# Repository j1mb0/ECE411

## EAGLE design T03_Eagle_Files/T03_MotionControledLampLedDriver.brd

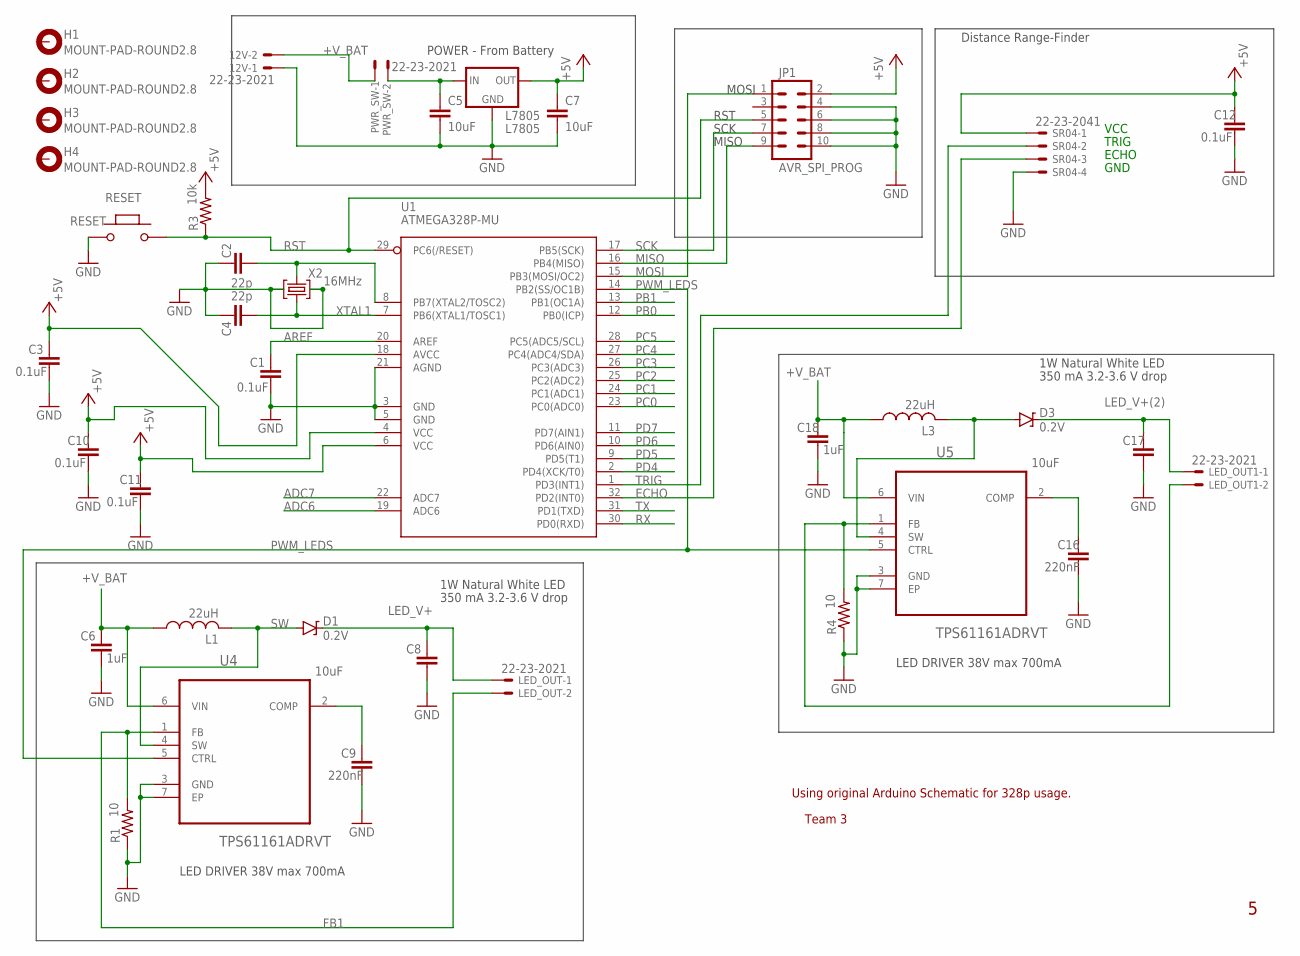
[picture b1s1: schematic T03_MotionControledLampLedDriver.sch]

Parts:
12V: 22-23-2021
C1, C3, C10, C11, C12: 0.1uF; C0603-ROUND
C2, C4: 22p; C0603-ROUND
C5, C7: 10uF; C1206
C6, C18: 1uF; C0603-ROUND
C8, C17: 10uF; C0603-ROUND
C9, C16: 220nF; C0603-ROUND
D1, D3: 0.2V; SOD-323
H1, H2, H3, H4: MOUNT-PAD-ROUND2.8; 2,8-PAD
JP1: AVR_SPI_PROG; 2X5-SHROUDED_LOCK
L1, L3: 22uH; L4532P
L7805: L7805; 78XXL
LED_OUT, LED_OUT1: 22-23-2021
PWR_SW: 22-23-2021
R1, R4: 10; M1206
R3: 10k; M1206
RESET: RESET; SMD_157SW
SR04: 22-23-2041
U1: ATMEGA328P-MU; TQFP32-08
U4, U5: TPS61161ADRVT; SON65P200X200X80-7N
X2: 16MHz; CRYSTAL-3.2-2.5

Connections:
+5V: C3.2, C7.1, C10.2, C11.2, C12.2, JP1.2, L7805.OUT, R3.2, SR04.1, U1.4 (VCC), U1.6 (VCC), U1.18 (AVCC)
+V_BAT: 12V.2, C6.2, C18.2, L1.1, L3.1, PWR_SW.1, U4.6 (VIN), U5.6 (VIN)
ADC6: U1.19 (ADC6)
ADC7: U1.22 (ADC7)
AREF: C1.2, U1.20 (AREF)
COMP: C9.2, U4.2 (COMP)
COMP1: C16.2, U5.2 (COMP)
ECHO: SR04.3, U1.32 (PD2(INT0))
FB1: LED_OUT.2, R1.2, U4.1 (FB)
FB2: LED_OUT1.2, R4.2, U5.1 (FB)
GND: 12V.1, C1.1, C2.2, C3.1, C4.2, C5.2, C6.1, C7.2, C8.1, C9.1, C10.1, C11.1, C12.1, C16.1, C17.1, C18.1, JP1.4, JP1.6, JP1.8, JP1.10, L7805.GND, R1.1, R4.1, RESET.1, SR04.4, U1.3 (GND), U1.5 (GND), U1.21 (AGND), U4.3 (GND), U4.7 (EP), U5.3 (GND), U5.7 (EP), X2.2 (GND), X2.4 (GND)
LED_V+: C8.2, D1.C, LED_OUT.1
LED_V+(2): C17.2, D3.C, LED_OUT1.1
MISO: JP1.9, U1.16 (PB4(MISO))
MOSI: JP1.1, U1.15 (PB3(MOSI/OC2))
unnamed: C5.1, L7805.IN, PWR_SW.2
PB0: U1.12 (PB0(ICP))
PB1: U1.13 (PB1(OC1A))
PC0: U1.23 (PC0(ADC0))
PC1: U1.24 (PC1(ADC1))
PC2: U1.25 (PC2(ADC2))
PC3: U1.26 (PC3(ADC3))
PC4: U1.27 (PC4(ADC4/SDA))
PC5: U1.28 (PC5(ADC5/SCL))
PD4: U1.2 (PD4(XCK/T0))
PD5: U1.9 (PD5(T1))
PD6: U1.10 (PD6(AIN0))
PD7: U1.11 (PD7(AIN1))
PWM_LEDS: U1.14 (PB2(SS/OC1B)), U4.5 (CTRL), U5.5 (CTRL)
RST: JP1.5, R3.1, RESET.2, U1.29 (PC6(/RESET))
RX: U1.30 (PD0(RXD))
SCK: JP1.7, U1.17 (PB5(SCK))
SW: D1.A, L1.2, U4.4 (SW)
SW1: D3.A, L3.2, U5.4 (SW)
TRIG: SR04.2, U1.1 (PD3(INT1))
TX: U1.31 (PD1(TXD))
XTAL1: C4.1, U1.7 (PB6(XTAL1/TOSC1)), X2.1 (C1)
XTAL2: C2.1, U1.8 (PB7(XTAL2/TOSC2)), X2.3 (C2)

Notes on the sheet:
POWER - From Battery
Distance Range-Finder
RST
MISO
SCK
MOSI
LED DRIVER 38V max 700mA
1W Natural White LED
350 mA 3.2-3.6 V drop
Using original Arduino Schematic for 328p usage.
Team 3
VCC
TRIG
ECHO
GND

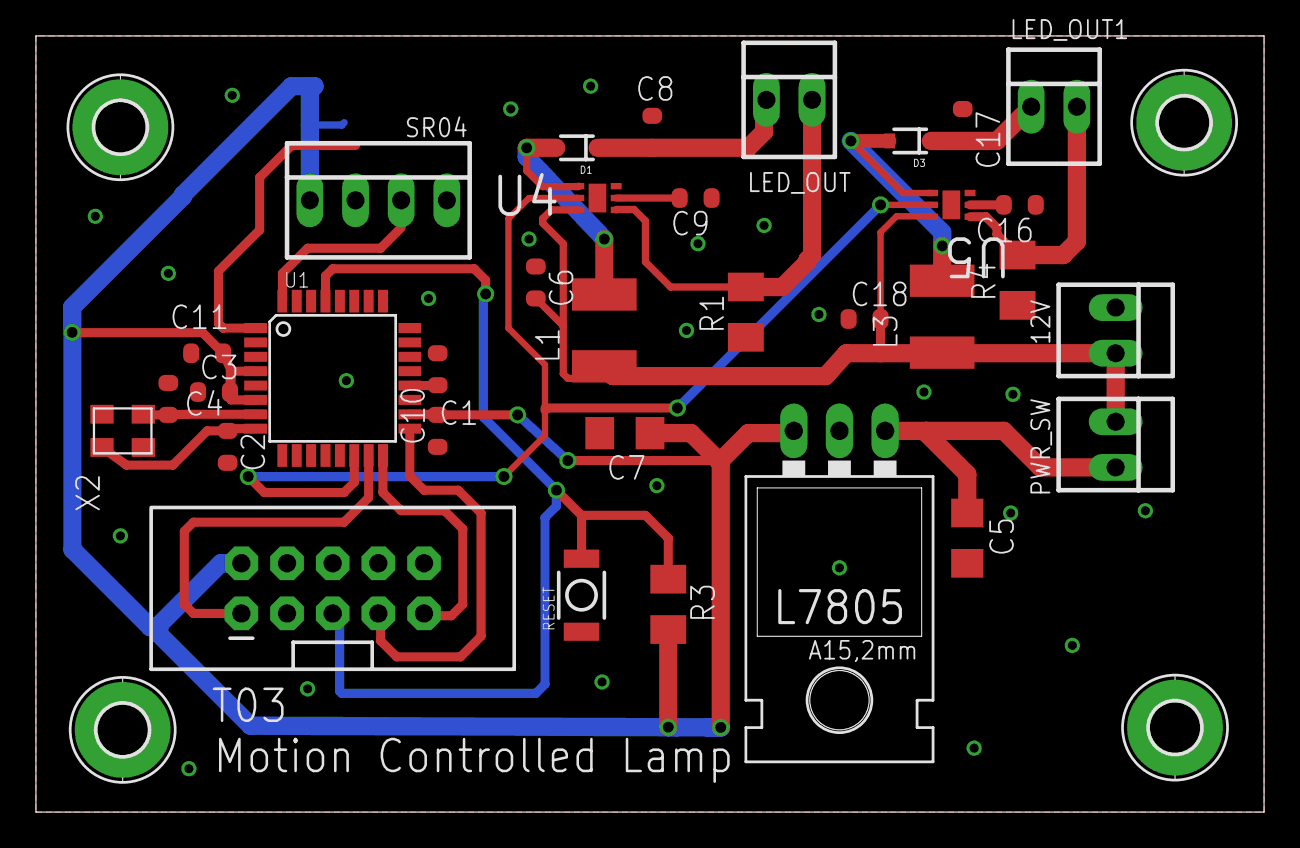
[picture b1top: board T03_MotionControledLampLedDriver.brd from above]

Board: 2 copper layers, 68.3 x 43.2 mm, 38 parts (1 on the bottom side), 22 nets.

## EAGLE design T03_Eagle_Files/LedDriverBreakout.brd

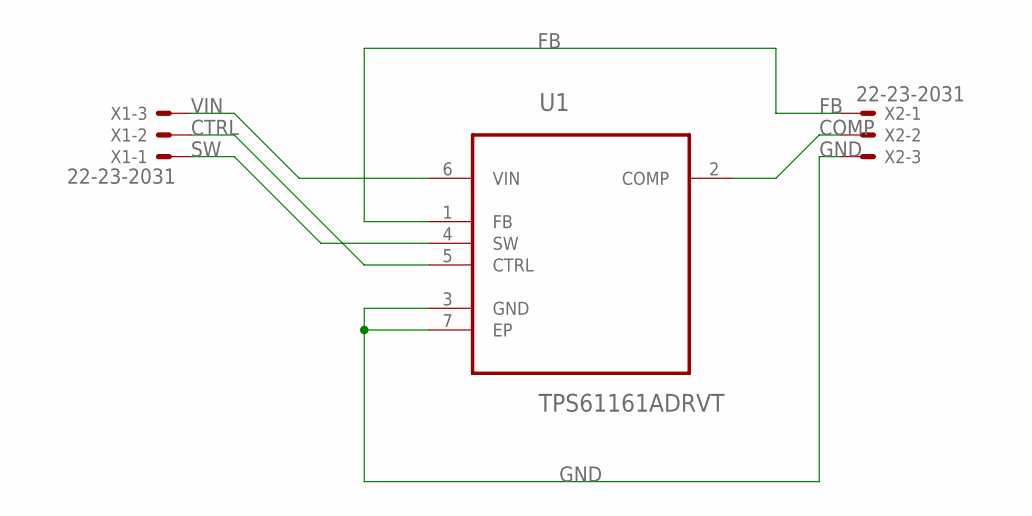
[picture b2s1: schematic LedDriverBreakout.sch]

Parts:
U1: TPS61161ADRVT; SON65P200X200X80-7N
X1, X2: 22-23-2031

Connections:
COMP: U1.2 (COMP), X2.2
CTRL: U1.5 (CTRL), X1.2
FB: U1.1 (FB), X2.1
GND: U1.3 (GND), U1.7 (EP), X2.3
SW: U1.4 (SW), X1.1
VIN: U1.6 (VIN), X1.3

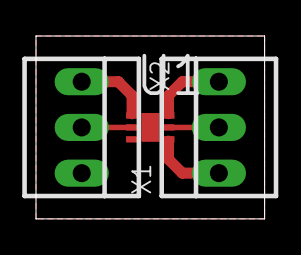
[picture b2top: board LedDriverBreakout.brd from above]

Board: 2 copper layers, 12.7 x 10.2 mm, 3 parts (0 on the bottom side), 6 nets.

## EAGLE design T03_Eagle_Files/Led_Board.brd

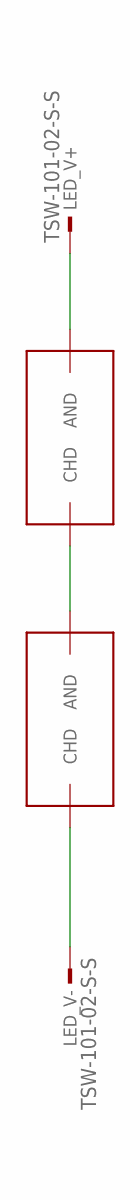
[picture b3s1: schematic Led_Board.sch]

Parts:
LED_V+: TSW-101-02-S-S
LED_V-: TSW-101-02-S-S
U$1, U$2: TL1F2-NW1

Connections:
unnamed: LED_V-.1, U$2.CATHODE (CHD)
unnamed: U$1.CATHODE (CHD), U$2.ANODE (AND)
unnamed: LED_V+.1, U$1.ANODE (AND)

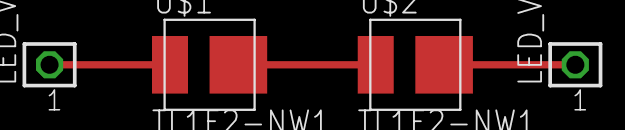
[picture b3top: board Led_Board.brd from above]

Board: 2 copper layers, 4 parts (0 on the bottom side), 3 nets.

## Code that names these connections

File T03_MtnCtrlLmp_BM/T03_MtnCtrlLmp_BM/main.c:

/*
 * T03_MtnCtrlLmp_BM.c
 *
 * Created: 11/27/2015 10:10:34 AM
 * Author : J1mb0
 * Motion Controlled Lamp using SR04 Ultrasonic Sensor
 * And custom Power NFET LED Driver.
 * 16 Mhz 62.5 ns Clock
 * Use prescale of 256 to get 16 us resolution on clock
 * with a range of 4 mS
 * Want response under 10 ms
 * Maybe not possible, SR04 has recommended read cycle of at least 60 ms
 */ 

#include <avr/io.h>
#define F_CPU 16000000UL //16 MHz
#include <util/delay.h>

#define MAX_PULSE_WIDTH 139 // 16 us * 139 ~= 2220 us
#define TIME_OUT 60		// 60 ms measurement cycle
#define MILLI_SECOND 64 // 16 us * 64 = 1024 uS or 1 mS 
#define US_ERROR 0xFFFF
// Ultrasonic Sensor (US) pin configuration
#define US_PORT PORTD
#define US_PIN PIND
#define US_DDR DDRD
#define US_ECHO_POS PORTD2
#define US_TRIG_POS PORTD3
// PWM conversion factors
#define MINIMUM_DISTANCE 27 // (3 in * 148)/ 16 uS = 27.75 rounded down 
#define MICROSEC_TO_PWM 2.28f // 2^8 / (139 - 27) ~= 2.28, our conversion factor

uint16_t getPulseWidth()
{
	uint16_t i, savedTimer, result, millisCount;
	
	i = 0;
	result = US_ERROR;		// Timed out code
	millisCount = 0;
	
	// set up timer
	TCCR0A = 0x00;
	TCCR0B = (1<<CS02);  // Prescaler = Fcpu/256
	TCNT0 = 0;			// Init Counter to 0
	
	// wait for the rising edge of ECHO or until time out
	while(millisCount < TIME_OUT && !(US_PIN & (1<<US_ECHO_POS)))
	{
		if(TCNT0 >= MILLI_SECOND)
		{
			TCNT0 = 0;
			millisCount++;
		}
	}
	// stop timer - I DO NOT THINK WE NEED TO DO THIS
	//CCR0B = 0x00 
	// Reset the timer
	//TCNT0 = 0;
	// Start timer again 
	//TCCR0B |= (1<<CS02);
	savedTimer = TCNT0;
	
	// Now wait for the falling edge or for the measurement to time out
	while((i - savedTimer) < MAX_PULSE_WIDTH && US_PIN & (1<<US_ECHO_POS))
	{
		i = TCNT0;
	}
	
	// if it did not time out, save the timer value
	if(i < MAX_PULSE_WIDTH)
	{
		result = i;
	}
	
	while(millisCount < MILLI_SECOND)
	{
		if(TCNT0 >= MILLI_SECOND)
		{
			TCNT0 = 0;
			millisCount++;
		}
	}
	
	// TURN OFF TIMER0
	TCCR0B = 0x00;
	
	return result;	
}

int main(void)
{
    uint16_t  i, result, averageResult;
	uint8_t pwmOut;
	pwmOut = 0;
	
	// Set Output/Input modes for pins
	// PWM_LEDS (PB2) as output (set 1)
	DDRB |= (1<<DDB2);
	// TRIG (PD3) as output (set 1)
	US_DDR |= (1<<DDD3);
	_delay_us(10);
	// ECHO (PD2) as input (set 0) NOT NECESSARY DEFAULT IS INPUT
	// US_DDR &= (0b111111011);
	
	// configure timer 0 NOT NECESSARY HERE, is done in 
	// set prescaler = FCPU/256
	// TCCR0B |= (1<<CS02);
	// initialize counter
	// TCNT0 = 0;
	
	// configure PWM
	// Set non-inverting 8-bit  fast PWM with no pre-scaler (full Fclk)
	TCCR1A = 0x23;
	TCCR1B = 0x09;
	
    while (1) 
    {
		// Read from SR04
			// DESIRED: Average 4 or so readings. 
		averageResult = 0;
		for(i = 0; i < 4; i++)
		{
			// Give the SR04 TRIG pin a 15 us High Pulse
			US_PORT |= (1<<US_TRIG_POS);
			_delay_us(16);
			US_PORT &= (~(1<<US_TRIG_POS));
			
			result = getPulseWidth();
			if(result == US_ERROR)
			{
				// SR04 timed out. Reset everything.
				averageResult = 0;
				break;
			} else
			{
				averageResult += result;
			}
		}
		
		// convert to PWM 
		if(averageResult > 0 )
		{
			averageResult = averageResult >> 2; // divide by 4 to get average
			// now check if further than 3 inches away
			if(averageResult > MINIMUM_DISTANCE)
			{
				// if it is, convert it to our 16 bit PWM value
				pwmOut = (uint8_t) (averageResult - MINIMUM_DISTANCE) * MICROSEC_TO_PWM;
			}
			else
			{
				pwmOut = 0;
			}
		}
		
		// Set PWM out accordingly
		OCR1A = pwmOut;
    }
}

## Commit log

2015-10-27 Experimental Arudino Demo
2015-11-02 Adding schematics and board layout files
2015-11-02 Updated Schematic
2015-11-02 Implementing Feedback
2015-11-02 Removing poorly named files
2015-11-05 Adding Schedule
2015-11-06 Breakout Board Schematics + Layout
2015-11-06 Cleaned up LED driver breakoout for machining
2015-11-06 adding gitignore file for Eagle cruft
2015-11-08 Started routing. Has polygon ready. Just ratsnest and then name the polygon to GND
2015-11-09 Cleaning up eagle backup files
2015-11-09 Completed Board Layout First Draft
2015-11-09 Updated values of components and symbols for Board Layout
2015-11-09 Added molex headers to schematic
2015-11-09 Updated board layout for molex connects
2015-11-16 Board Layouts finished, ready for OSH
2015-11-23 The test plan for the project
2015-11-23 The detailed test cases for the project
2015-11-29 First draft of AVR Code done. Please code review
2015-12-06 Final Presentation and Schedule
2015-12-06 Test Results
2015-12-11 Adding Final Files
    Adding BOM and Final Iterations of the Presentation and Test Plan.

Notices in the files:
parts and their libraries:
SparkFun-DiscreteSemi: Licensing: Creative Commons ShareAlike 4.0 International - https://creativecommons.org/licenses/by-sa/4.0
